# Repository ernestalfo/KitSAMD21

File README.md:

Custom little board with the SAMD21 microcontroller with all the pins exposed.
[KiCAD project]

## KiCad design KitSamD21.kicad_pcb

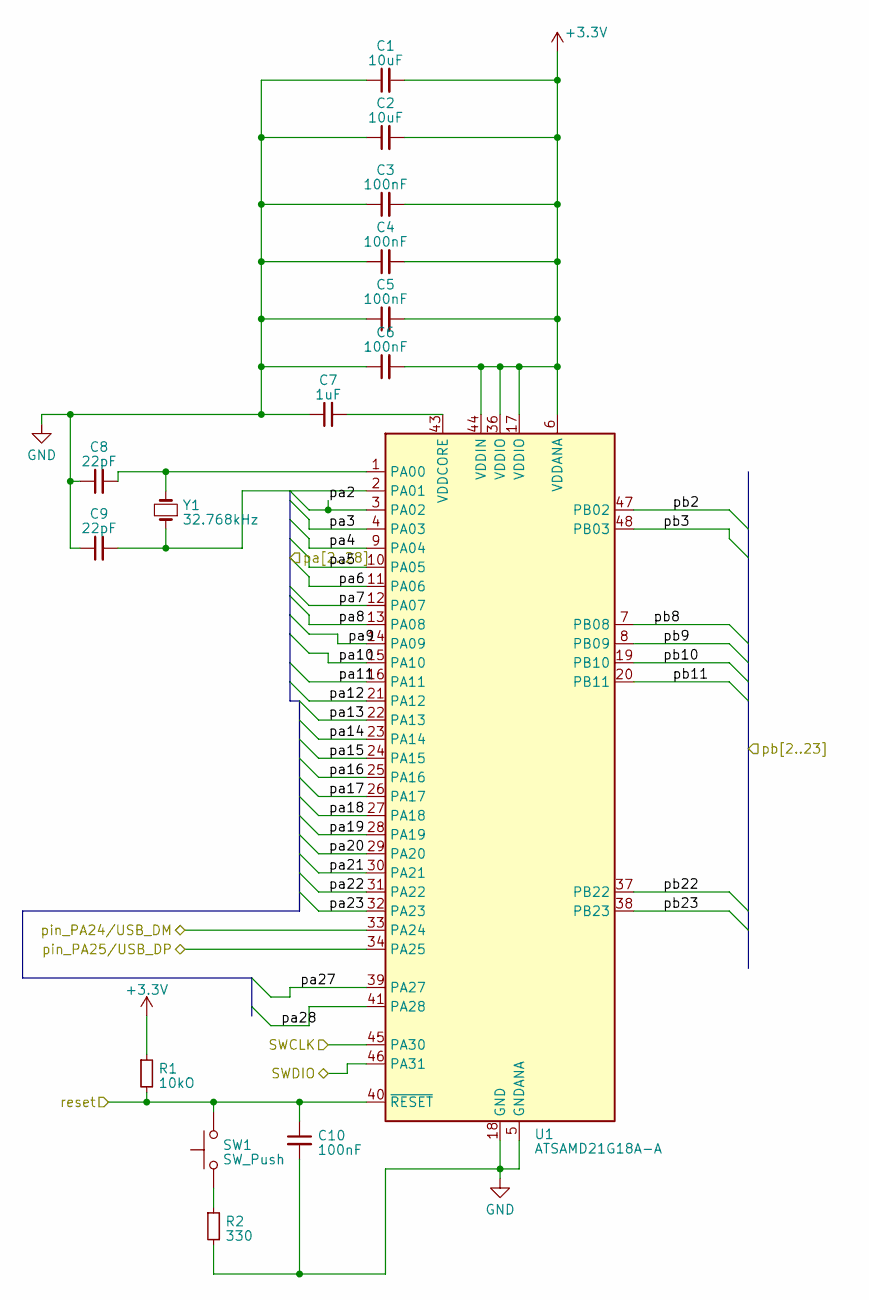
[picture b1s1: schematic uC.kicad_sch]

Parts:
C1, C2: 10uF; C_0603_1608Metric_Pad1.08x0.95mm_HandSolder
C3, C4, C5, C6, C10: 100nF; C_0603_1608Metric_Pad1.08x0.95mm_HandSolder
C7: 1uF; C_0603_1608Metric_Pad1.08x0.95mm_HandSolder
C8, C9: 22pF; C_0603_1608Metric_Pad1.08x0.95mm_HandSolder
R1: 10kO; R_0603_1608Metric_Pad0.98x0.95mm_HandSolder
R2: 330; R_0603_1608Metric_Pad0.98x0.95mm_HandSolder
SW1: SW_Push; SW_SPST_B3U-1000P
U1: ATSAMD21G18A-A; TQFP-48_7x7mm_P0.5mm
Y1: 32.768kHz; Crystal_SMD_3215-2Pin_3.2x1.5mm

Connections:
+3.3V: C1.2, C2.2, C3.2, C4.2, C5.2, C6.2, R1.1, U1.6 (VDDANA), U1.17 (VDDIO), U1.36 (VDDIO), U1.44 (VDDIN); also elsewhere on the board
/Connectors/pa2: U1.3 (PA02); also elsewhere on the board
/Connectors/pa3: U1.4 (PA03); also elsewhere on the board
/Connectors/pa4: U1.9 (PA04); also elsewhere on the board
/Connectors/pa5: U1.10 (PA05); also elsewhere on the board
/Connectors/pa6: U1.11 (PA06); also elsewhere on the board
/Connectors/pa7: U1.12 (PA07); also elsewhere on the board
/Connectors/pa8: U1.13 (PA08); also elsewhere on the board
/Connectors/pa9: U1.14 (PA09); also elsewhere on the board
/Connectors/pa10: U1.15 (PA10); also elsewhere on the board
/Connectors/pa11: U1.16 (PA11); also elsewhere on the board
/Connectors/pa12: U1.21 (PA12); also elsewhere on the board
/Connectors/pa13: U1.22 (PA13); also elsewhere on the board
/Connectors/pa14: U1.23 (PA14); also elsewhere on the board
/Connectors/pa15: U1.24 (PA15); also elsewhere on the board
/Connectors/pa16: U1.25 (PA16); also elsewhere on the board
/Connectors/pa17: U1.26 (PA17); also elsewhere on the board
/Connectors/pa18: U1.27 (PA18); also elsewhere on the board
/Connectors/pa19: U1.28 (PA19); also elsewhere on the board
/Connectors/pa20: U1.29 (PA20); also elsewhere on the board
/Connectors/pa21: U1.30 (PA21); also elsewhere on the board
/Connectors/pa22: U1.31 (PA22); also elsewhere on the board
/Connectors/pa23: U1.32 (PA23); also elsewhere on the board
/Connectors/pa27: U1.39 (PA27); also elsewhere on the board
/Connectors/pa28: U1.41 (PA28); also elsewhere on the board
/Connectors/pb2: U1.47 (PB02); also elsewhere on the board
/Connectors/pb3: U1.48 (PB03); also elsewhere on the board
/Connectors/pb8: U1.7 (PB08); also elsewhere on the board
/Connectors/pb9: U1.8 (PB09); also elsewhere on the board
/Connectors/pb10: U1.19 (PB10); also elsewhere on the board
/Connectors/pb11: U1.20 (PB11); also elsewhere on the board
/Connectors/pb22: U1.37 (PB22); also elsewhere on the board
/Connectors/pb23: U1.38 (PB23); also elsewhere on the board
/Connectors/pin_PA24/USB_DM: U1.33 (PA24); also elsewhere on the board
/Connectors/pin_PA25/USB_DP: U1.34 (PA25); also elsewhere on the board
GND: C1.1, C2.1, C3.1, C4.1, C5.1, C6.1, C7.1, C8.1, C9.1, C10.2, R2.2, U1.5 (GNDANA), U1.18 (GND), U1.35 (GND), U1.42 (GND); also elsewhere on the board
JTAG_SWCLK: U1.45 (PA30); also elsewhere on the board
JTAG_SWDIO: U1.46 (PA31); also elsewhere on the board
JTAG_reset: C10.1, R1.2, SW1.2, U1.40 (~RESET); also elsewhere on the board
unnamed: R2.1, SW1.1
unnamed: C8.2, U1.1 (PA00), Y1.2
unnamed: C9.2, U1.2 (PA01), Y1.1
unnamed: C7.2, U1.43 (VDDCORE)

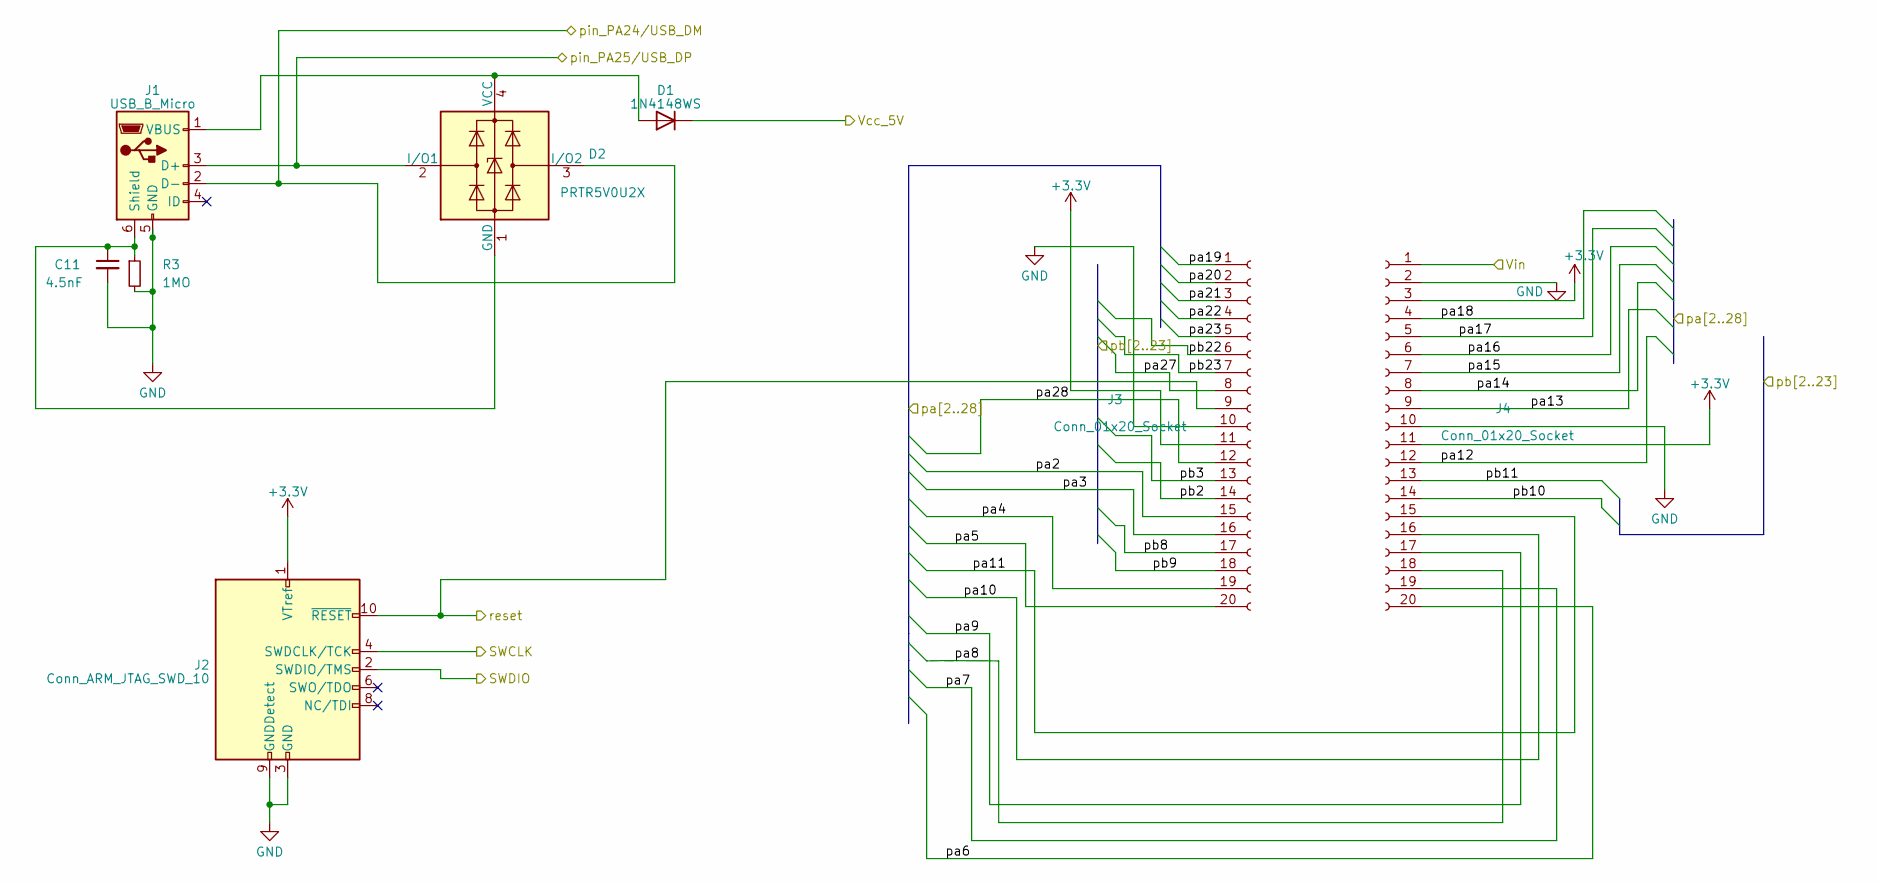
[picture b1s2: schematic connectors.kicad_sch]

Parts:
C11: 4.5nF; C_0603_1608Metric_Pad1.08x0.95mm_HandSolder
D1: 1N4148WS; D_SOD-323_HandSoldering
D2: PRTR5V0U2X; SOT-143
J1: USB_B_Micro; USB3131-30-0230-A
J2: Conn_ARM_JTAG_SWD_10; Tag-Connect_TC2050-IDC-NL_2x05_P1.27mm_Vertical
J3, J4: Conn_01x20_Socket; PinHeader_1x20_P2.54mm_Vertical
R3: 1MO; R_0603_1608Metric_Pad0.98x0.95mm_HandSolder

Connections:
+3.3V: J2.1 (VTref), J3.11, J4.3, J4.11; also elsewhere on the board
/Connectors/Vcc_5V: D1.1 (K); also elsewhere on the board
/Connectors/Vin: J4.1; also elsewhere on the board
/Connectors/pa2: J3.15; also elsewhere on the board
/Connectors/pa3: J3.16; also elsewhere on the board
/Connectors/pa4: J3.19; also elsewhere on the board
/Connectors/pa5: J3.20; also elsewhere on the board
/Connectors/pa6: J4.20; also elsewhere on the board
/Connectors/pa7: J4.19; also elsewhere on the board
/Connectors/pa8: J4.18; also elsewhere on the board
/Connectors/pa9: J4.17; also elsewhere on the board
/Connectors/pa10: J4.16; also elsewhere on the board
/Connectors/pa11: J4.15; also elsewhere on the board
/Connectors/pa12: J4.12; also elsewhere on the board
/Connectors/pa13: J4.9; also elsewhere on the board
/Connectors/pa14: J4.8; also elsewhere on the board
/Connectors/pa15: J4.7; also elsewhere on the board
/Connectors/pa16: J4.6; also elsewhere on the board
/Connectors/pa17: J4.5; also elsewhere on the board
/Connectors/pa18: J4.4; also elsewhere on the board
/Connectors/pa19: J3.1; also elsewhere on the board
/Connectors/pa20: J3.2; also elsewhere on the board
/Connectors/pa21: J3.3; also elsewhere on the board
/Connectors/pa22: J3.4; also elsewhere on the board
/Connectors/pa23: J3.5; also elsewhere on the board
/Connectors/pa27: J3.8; also elsewhere on the board
/Connectors/pa28: J3.12; also elsewhere on the board
/Connectors/pb2: J3.14; also elsewhere on the board
/Connectors/pb3: J3.13; also elsewhere on the board
/Connectors/pb8: J3.17; also elsewhere on the board
/Connectors/pb9: J3.18; also elsewhere on the board
/Connectors/pb10: J4.14; also elsewhere on the board
/Connectors/pb11: J4.13; also elsewhere on the board
/Connectors/pb22: J3.6; also elsewhere on the board
/Connectors/pb23: J3.7; also elsewhere on the board
/Connectors/pin_PA24/USB_DM: D2.3 (I/O2), J1.2 (D-); also elsewhere on the board
/Connectors/pin_PA25/USB_DP: D2.2 (I/O1), J1.3 (D+); also elsewhere on the board
GND: C11.2, J1.5 (GND), J2.3 (GND), J2.5 (GND), J2.9 (GNDDetect), J3.10, J4.2, J4.10, R3.2; also elsewhere on the board
JTAG_SWCLK: J2.4 (SWDCLK/TCK); also elsewhere on the board
JTAG_SWDIO: J2.2 (SWDIO/TMS); also elsewhere on the board
JTAG_reset: J2.10 (~RESET), J3.9; also elsewhere on the board
unnamed: D1.2 (A), D2.4 (VCC), J1.1 (VBUS)
unnamed: C11.1, D2.1 (GND), J1.6 (Shield), R3.1

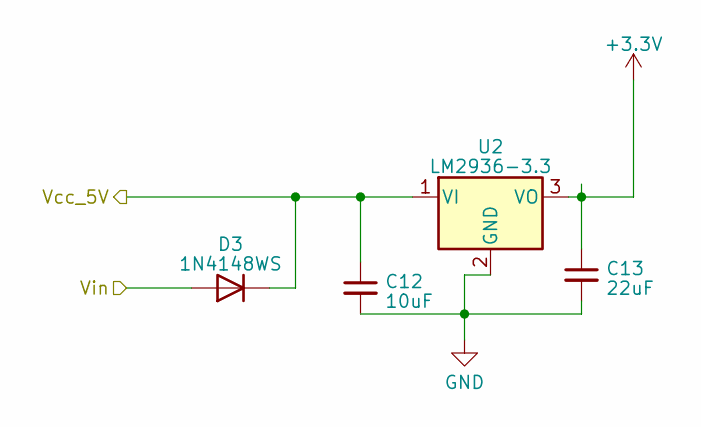
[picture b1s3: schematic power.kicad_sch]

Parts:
C12: 10uF; C_0603_1608Metric_Pad1.08x0.95mm_HandSolder
C13: 22uF; C_0603_1608Metric_Pad1.08x0.95mm_HandSolder
D3: 1N4148WS; D_SOD-323_HandSoldering
U2: LM2936-3.3; SOT-223-3_TabPin2

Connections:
+3.3V: C13.1, U2.3 (VO); also elsewhere on the board
/Connectors/Vcc_5V: C12.1, D3.1 (K), U2.1 (VI); also elsewhere on the board
/Connectors/Vin: D3.2 (A); also elsewhere on the board
GND: C12.2, C13.2, U2.2 (GND); also elsewhere on the board

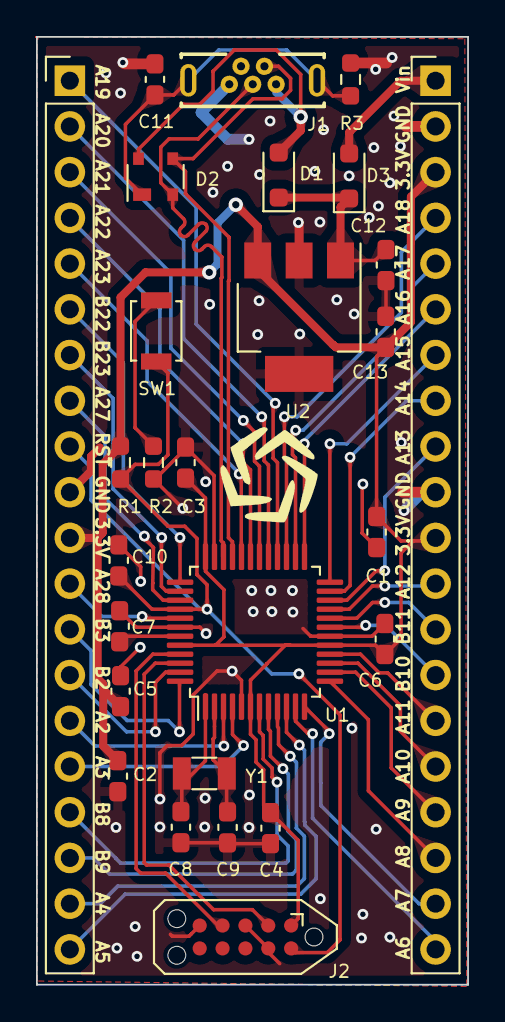
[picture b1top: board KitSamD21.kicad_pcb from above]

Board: 2 copper layers, 24.0 x 52.7 mm, 27 parts (0 on the bottom side), 47 nets.
